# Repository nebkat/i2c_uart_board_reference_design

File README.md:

# NXP Semiconductors SC16IS752 Breakout Board

This repository contains KiCAD schematics and the PCB design for a breakout board for the SC16IS752.

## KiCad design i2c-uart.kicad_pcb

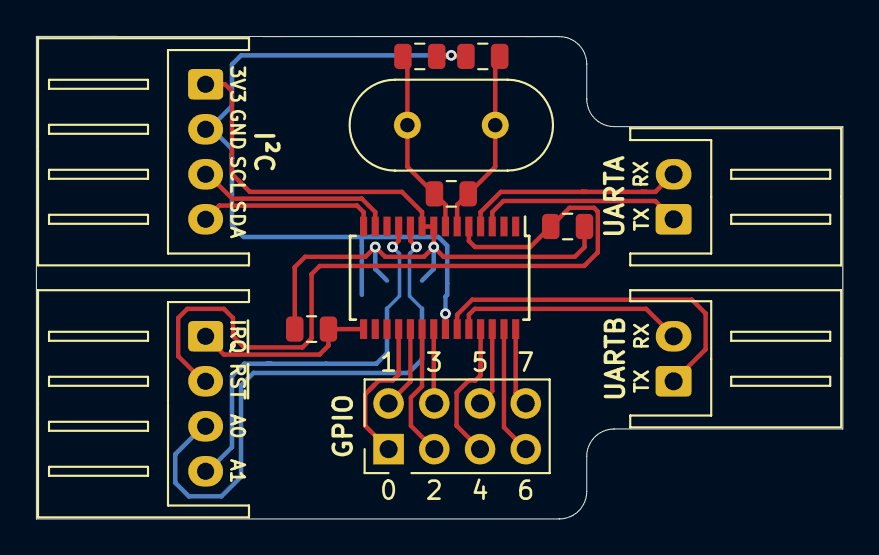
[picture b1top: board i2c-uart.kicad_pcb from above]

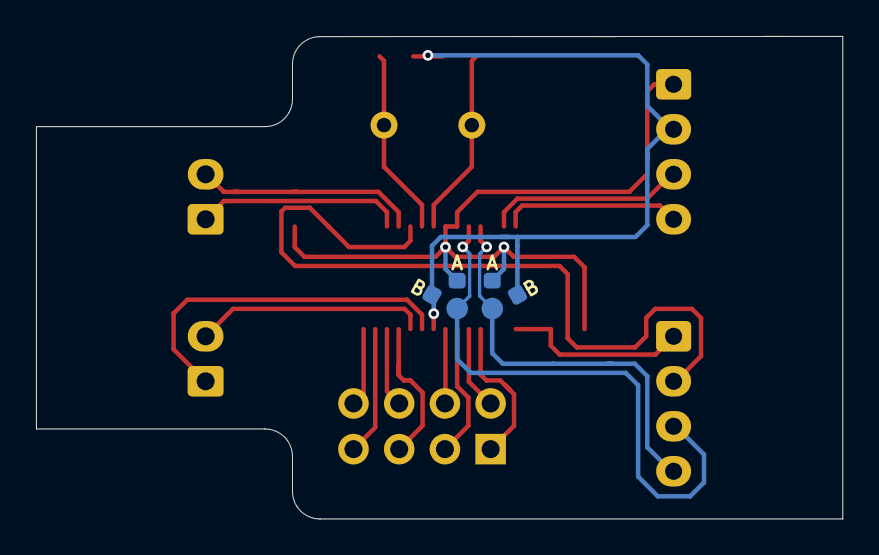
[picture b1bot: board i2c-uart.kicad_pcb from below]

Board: 2 copper layers, 44.8 x 26.8 mm, 14 parts (2 on the bottom side), 22 nets.

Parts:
C1, C2: 36pF; C_0805_2012Metric
J1: Conn_UARTA; JST_XH_S02B-XH-A_1x02_P2.50mm_Horizontal
J2: Conn_UARTB; JST_XH_S02B-XH-A_1x02_P2.50mm_Horizontal
J3: Conn_IO; PinHeader_2x04_P2.54mm_Vertical
J4: Conn_I2C; JST_XH_S04B-XH-A_1x04_P2.50mm_Horizontal
J5: Conn_Extra; JST_XH_S04B-XH-A_1x04_P2.50mm_Horizontal
R1, R6: 1k; R_0805_2012Metric
R5: 1M; R_0805_2012Metric
SW1: SW_0R; SW_0R_x2_0603_Mirror
SW2: SW_0R; SW_0R_x2_0603
U1: SC16IS752IPW; TSSOP-28_4.4x9.7mm_P0.65mm
Y1: 14.7456MHz; Crystal_HC49-U_Vertical

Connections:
+3V3: J4.1, R1.2, R6.2, SW1.1, SW2.1, U1.8, U1.9
/IO0: J3.1, U1.18
/IO1: J3.2, U1.19
/IO2: J3.3, U1.20
/IO3: J3.4, U1.21
/IO4: J3.5, U1.25
/IO5: J3.6, U1.26
/IO6: J3.7, U1.27
/IO7: J3.8, U1.28
/RXA: J1.2, U1.4
/RXB: J2.2, U1.24
/TXA: J1.1, U1.3
/TXB: J2.1, U1.23
/XTAL1: C1.1, R5.2, U1.6, Y1.1
/XTAL2: C2.1, R5.1, U1.7, Y1.2
A0: J5.3, SW1.2, U1.10
A1: J5.4, SW2.2, U1.11
GND: C1.2, C2.2, J4.2, SW1.3, SW2.3, U1.22
IRQ: J5.1, R6.1, U1.15
RESET: J5.2, R1.1, U1.5
SCL: J4.3, U1.13
SDA: J4.4, U1.14
